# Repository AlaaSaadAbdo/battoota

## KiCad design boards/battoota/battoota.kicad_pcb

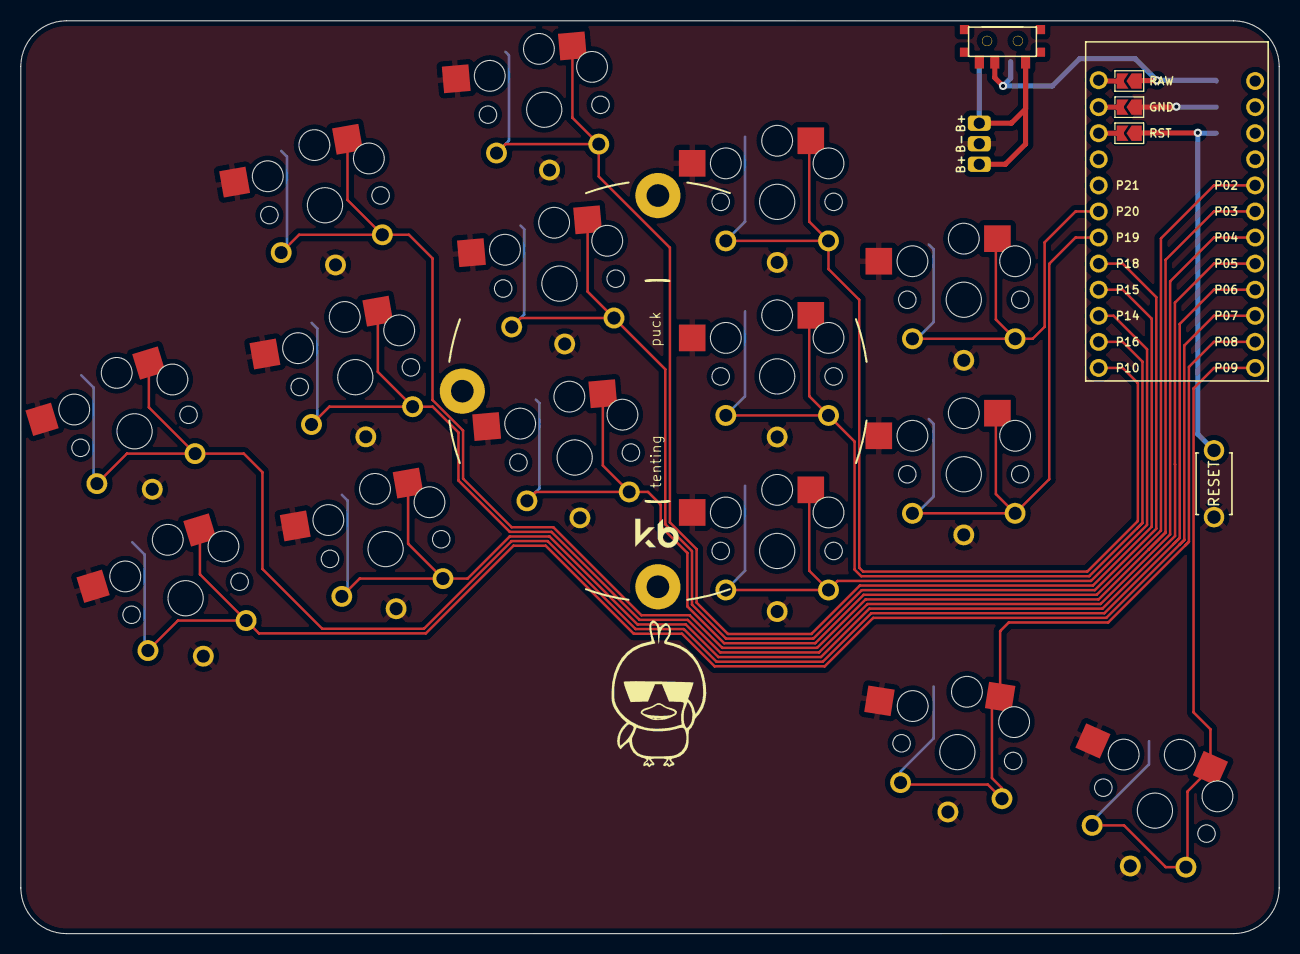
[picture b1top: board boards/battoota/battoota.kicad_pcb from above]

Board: 2 copper layers, 122.6 x 88.9 mm, 20 parts (0 on the bottom side), 19 nets.

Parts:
B1: ResetSW
MCU1: ProMicro
PAD1: bat
S3, S5, S7, S9, S11, S13, S15, S17, S19, S21, S23, S27, S29, S31, S33: choc_hotswap_key
T1, T2: SPDT_C128955

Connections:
Braw: PAD1.1, PAD1.3, T1.1, T2.1
GND: B1.2, MCU1.2, PAD1.2, S3.2, S5.2, S7.2, S9.2, S11.2, S13.2, S15.2, S17.2, S19.2, S21.2, S23.2, S27.2, S29.2, S31.2, S33.2
P2: MCU1.17, S13.1
P3: MCU1.18, S11.1
P4: MCU1.19, S9.1
P5: MCU1.20, S7.1
P6: MCU1.21, S5.1
P7: MCU1.22, S3.1
P8: MCU1.23, S31.1
P9: MCU1.24, S33.1
P10: MCU1.12, S23.1
P14: MCU1.10, S19.1
P15: MCU1.9, S17.1
P16: MCU1.11, S21.1
P18: MCU1.8, S15.1
P19: MCU1.7, S27.1
P20: MCU1.6, S29.1
RAW: MCU1.1, T1.2, T2.2
RST: B1.1, MCU1.3

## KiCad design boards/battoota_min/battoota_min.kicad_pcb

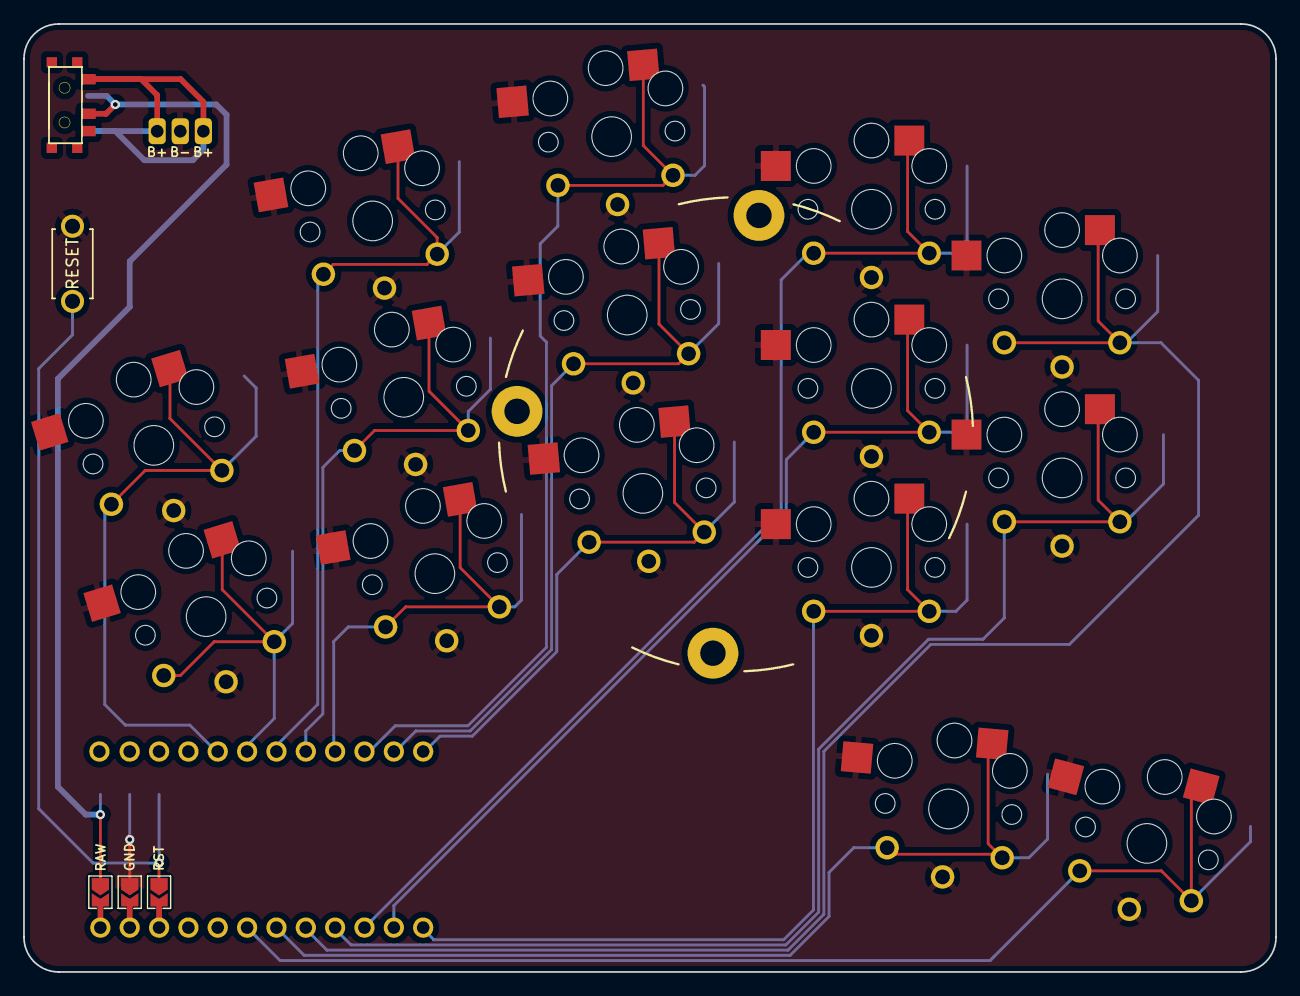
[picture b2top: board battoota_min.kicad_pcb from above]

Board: 2 copper layers, 108.4 x 82.1 mm, 20 parts (1 on the bottom side), 19 nets.

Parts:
B1: ResetSW
MCU1: ProMicro32keys
PAD1: bat
S1, S2, S3, S4, S5, S6, S7, S8, S9, S10, S11, S12, S13, S14, S15: key
T1, T2: SPDT_C128955

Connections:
BRAW: PAD1.1, PAD1.3, T1.1, T2.1
GND: B1.1, MCU1.2, PAD1.2, S1.1, S1.2, S2.1, S2.2, S3.1, S3.2, S4.1, S4.2, S5.1, S5.2, S6.1, S6.2, S7.1, S7.2, S8.1, S8.2, S9.1, S9.2, S10.1, S10.2, S11.1, S11.2, S12.1, S12.2, S13.1, S13.2, S14.1, S14.2, S15.1, S15.2
P3: MCU1.18, S15.1, S15.2
P4: MCU1.19, S14.1, S14.2
P5: MCU1.20, S13.1, S13.2
P6: MCU1.21, S12.1, S12.2
P7: MCU1.22, S11.1, S11.2
P8: MCU1.23, S10.1, S10.2
P9: MCU1.24, S9.1, S9.2
P10: MCU1.12, S6.1, S6.2
P14: MCU1.10, S8.1, S8.2
P15: MCU1.9, S3.1, S3.2
P16: MCU1.11, S7.1, S7.2
P18: MCU1.8, S4.1, S4.2
P19: MCU1.7, S5.1, S5.2
P20: MCU1.6, S1.1, S1.2
P21: MCU1.5, S2.1, S2.2
RAW: MCU1.1, T1.2, T2.2
RST: B1.2, MCU1.3

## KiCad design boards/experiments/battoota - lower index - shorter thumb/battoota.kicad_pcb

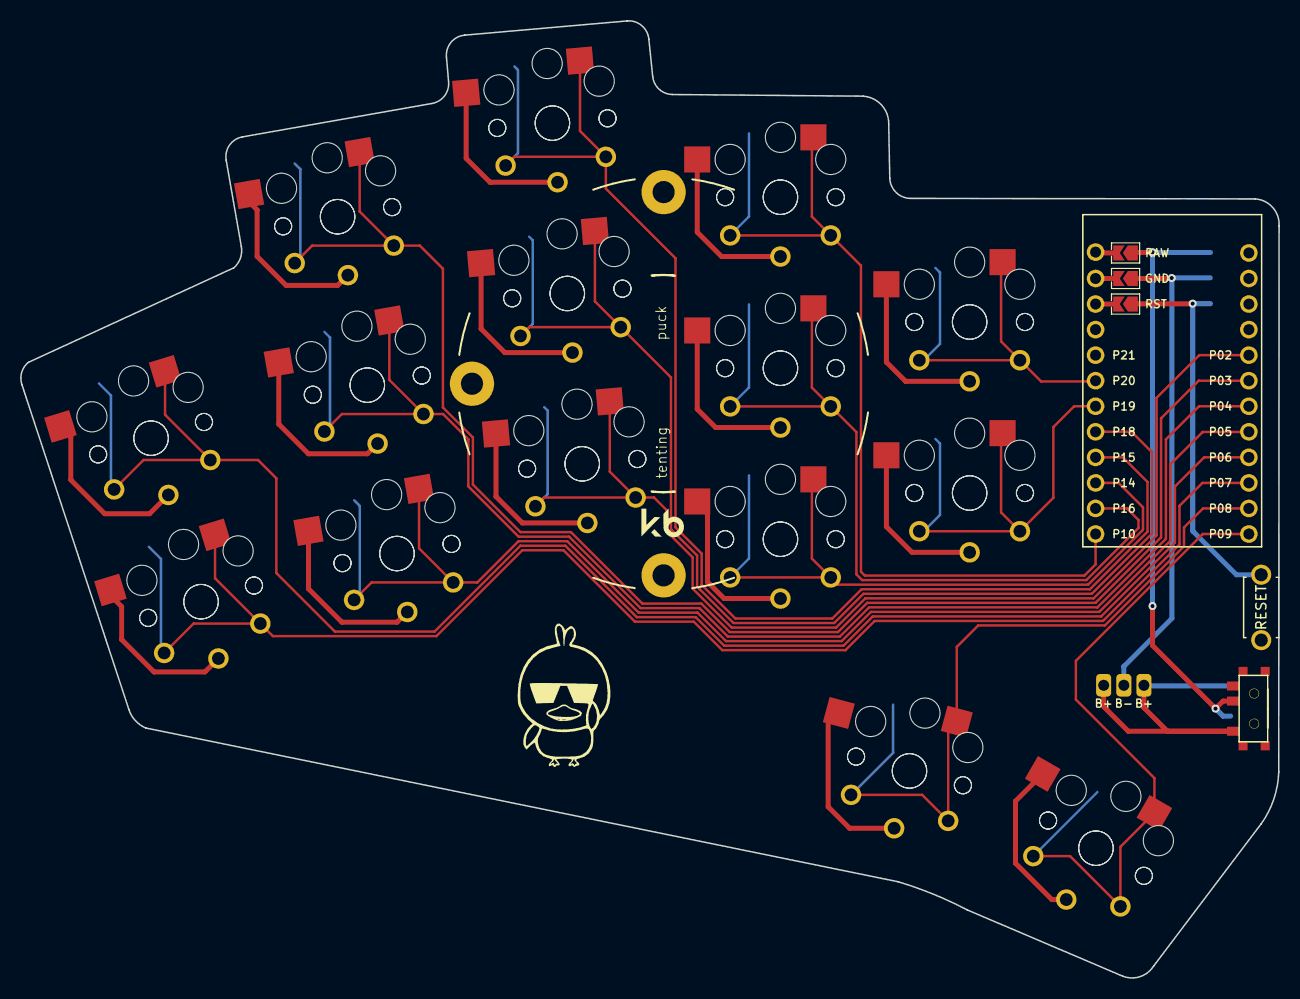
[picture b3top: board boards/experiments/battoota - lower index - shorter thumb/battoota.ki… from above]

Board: 2 copper layers, 125.1 x 95.1 mm, 35 parts (0 on the bottom side), 19 nets.

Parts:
B1: ResetSW
MCU1: ProMicro
PAD1: bat
S3, S4, S5, S6, S7, S8, S9, S10, S11, S12, S13, S14, S15, S16, S17, S18, S19, S20, S21, S22, S23, S24, S27, S28, S29, S30, S31, S32, S33, S34: PG1350
T1, T2: SPDT_C128955

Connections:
Braw: PAD1.1, PAD1.3, T1.1, T2.1
GND: B1.2, MCU1.2, PAD1.2, S3.2, S4.2, S5.2, S6.2, S7.2, S8.2, S9.2, S10.2, S11.2, S12.2, S13.2, S14.2, S15.2, S16.2, S17.2, S18.2, S19.2, S20.2, S21.2, S22.2, S23.2, S24.2, S27.2, S28.2, S29.2, S30.2, S31.2, S32.2, S33.2, S34.2
P2: MCU1.17, S13.1, S14.1
P3: MCU1.18, S11.1, S12.1
P4: MCU1.19, S9.1, S10.1
P5: MCU1.20, S7.1, S8.1
P6: MCU1.21, S5.1, S6.1
P7: MCU1.22, S3.1, S4.1
P8: MCU1.23, S31.1, S32.1
P9: MCU1.24, S33.1, S34.1
P10: MCU1.12, S23.1, S24.1
P14: MCU1.10, S19.1, S20.1
P15: MCU1.9, S17.1, S18.1
P16: MCU1.11, S21.1, S22.1
P18: MCU1.8, S15.1, S16.1
P19: MCU1.7, S27.1, S28.1
P20: MCU1.6, S29.1, S30.1
RAW: MCU1.1, T1.2, T2.2
RST: B1.1, MCU1.3
